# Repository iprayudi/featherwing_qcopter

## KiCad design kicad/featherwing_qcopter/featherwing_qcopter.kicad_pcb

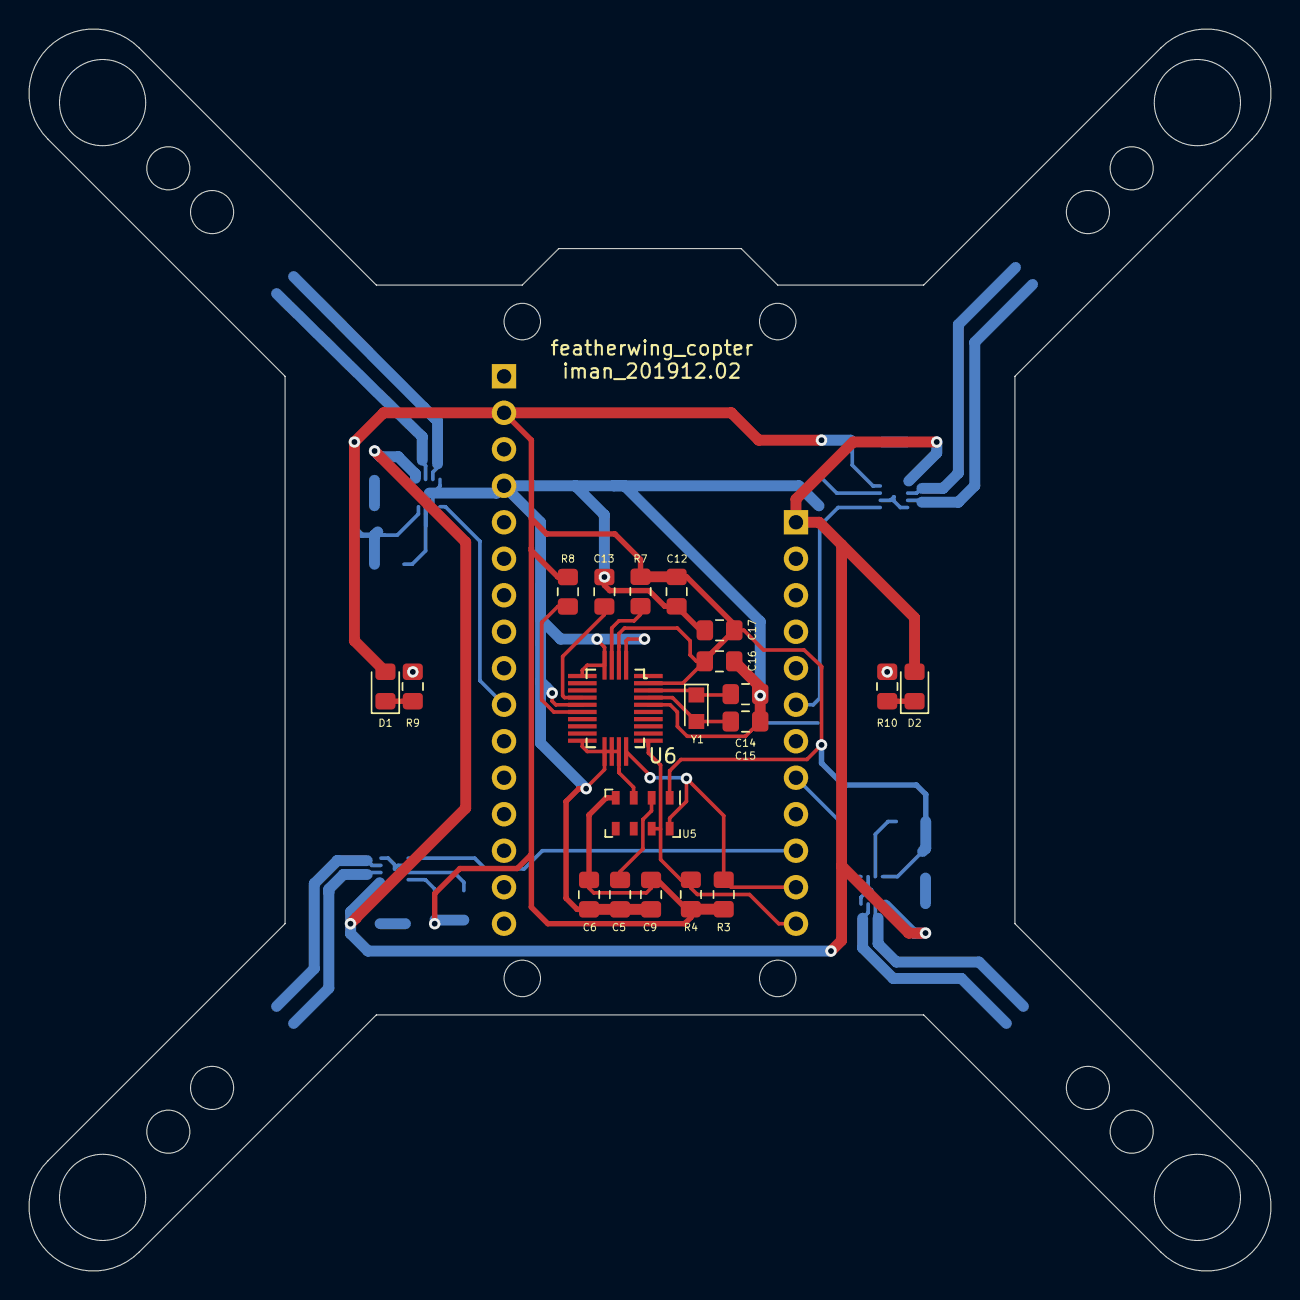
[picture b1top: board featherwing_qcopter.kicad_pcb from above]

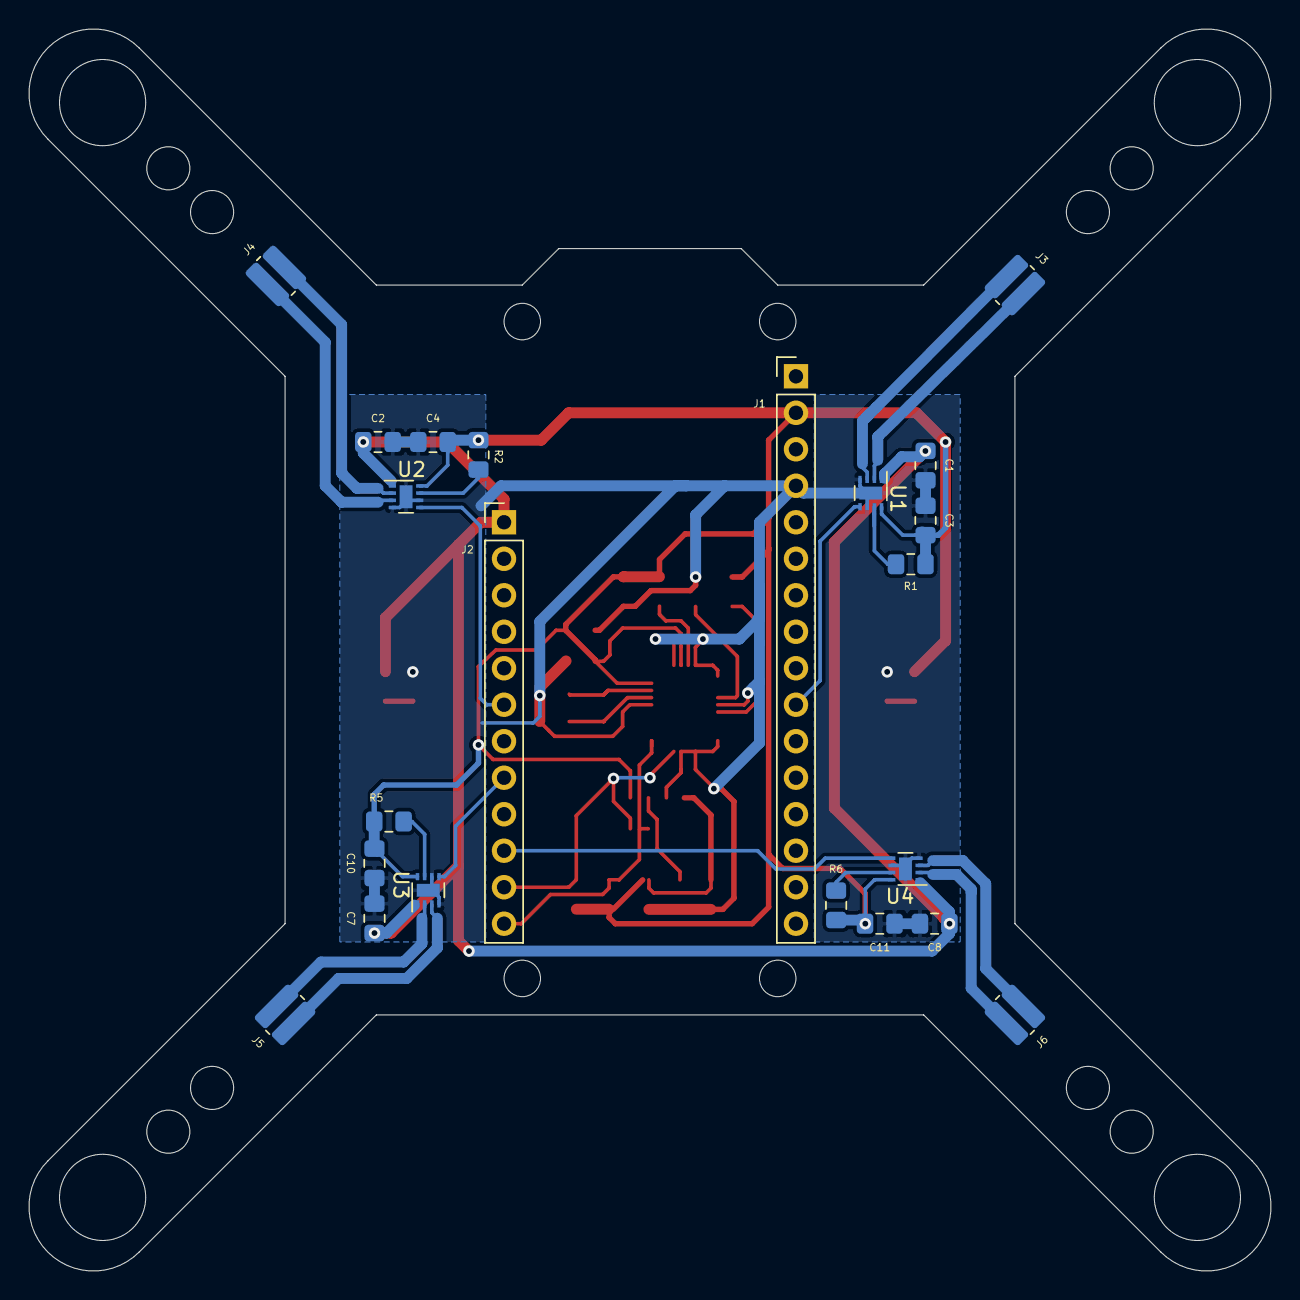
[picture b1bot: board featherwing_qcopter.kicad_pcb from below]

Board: 2 copper layers, 86.4 x 86.4 mm, 42 parts (22 on the bottom side), 29 nets.

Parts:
C1, C2, C3, C4, C5, C7, C8, C9, C10, C11, C12, C13: 100n; C_0805_2012Metric_Pad1.15x1.40mm_HandSolder
C6: 10u; C_0805_2012Metric_Pad1.15x1.40mm_HandSolder
C14, C15: 22p; C_0805_2012Metric_Pad1.15x1.40mm_HandSolder
C16: 120n; C_0805_2012Metric_Pad1.15x1.40mm_HandSolder
C17: 6.8n; C_0805_2012Metric_Pad1.15x1.40mm_HandSolder
D1, D2: LED; LED_0805_2012Metric_Pad1.15x1.40mm_HandSolder
J1: Conn_01x16_Male; PinHeader_1x16_P2.54mm_Vertical
J2: Conn_01x12_Male; PinHeader_1x12_P2.54mm_Vertical
J3, J4, J5, J6: Motor connector; R_0612_1632Metric_Pad1.18x3.40mm_HandSolder
R1, R2, R3, R4, R5, R6, R7, R8, R9, R10: 10k; R_0805_2012Metric_Pad1.15x1.40mm_HandSolder
U1, U2, U3, U4: DRV8837CDSGR; WSON-8-1EP_2x2mm_P0.5mm_EP0.9x1.6mm
U5: MPL3115A2; LGA-8_3x5mm_P1.25mm
U6: BNO055; LGA-28_5.2x3.8mm_BNO0055_handsoldering
Y1: 32.768k; Crystal_SMD_2012-2Pin_2.0x1.2mm_HandSoldering

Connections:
+3V3: C3.2, C4.2, C5.2, C6.1, C10.2, C11.2, C12.2, C16.2, C17.2, D1.2, J1.2, R1.2, R2.2, R3.1, R4.1, R5.2, R6.2, R7.1, R8.1, U1.8, U2.8, U3.8, U4.8, U5.1, U5.4, U6.3, U6.28
/BAT: C1.1, C2.1, C7.1, C8.1, D2.2, J2.1, U1.1, U2.1, U3.1, U4.1
/SCL: J2.11, R3.2, U5.8, U6.19
/SDA: J2.12, R4.2, U5.7, U6.20
/p14: J2.10, U4.5
/p15: J2.8, U3.5
/p27: J2.6, U2.5
/pA5: J1.10, U1.5
GND: C1.2, C2.2, C3.1, C4.1, C5.1, C6.2, C7.2, C8.2, C9.2, C10.1, C11.1, C12.1, C13.1, C14.2, C15.1, C16.1, C17.1, J1.4, R9.2, R10.2, U1.4, U1.6, U1.9, U2.4, U2.6, U2.9, U3.4, U3.6, U3.9, U4.4, U4.6, U4.9, U5.3, U6.2, U6.5, U6.6, U6.10, U6.15, U6.16, U6.17, U6.18, U6.25
unnamed: C9.1, U5.2
unnamed: C13.2, U6.9
unnamed: C14.1, U6.26, Y1.2
unnamed: C15.2, U6.27, Y1.1
unnamed: D1.1, R9.1
unnamed: D2.1, R10.1
unnamed: J3.1, U1.3
unnamed: J3.2, U1.2
unnamed: J4.1, U2.3
unnamed: J4.2, U2.2
unnamed: J5.1, U3.3
unnamed: J5.2, U3.2
unnamed: J6.1, U4.3
unnamed: J6.2, U4.2
unnamed: R1.1, U1.7
unnamed: R2.1, U2.7
unnamed: R5.1, U3.7
unnamed: R6.1, U4.7
unnamed: R7.2, U6.4
unnamed: R8.2, U6.11

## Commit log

2019-12-29 schematic updated
2019-12-30 repository updated
2020-01-21 removed temp files
2020-01-28 added codes
